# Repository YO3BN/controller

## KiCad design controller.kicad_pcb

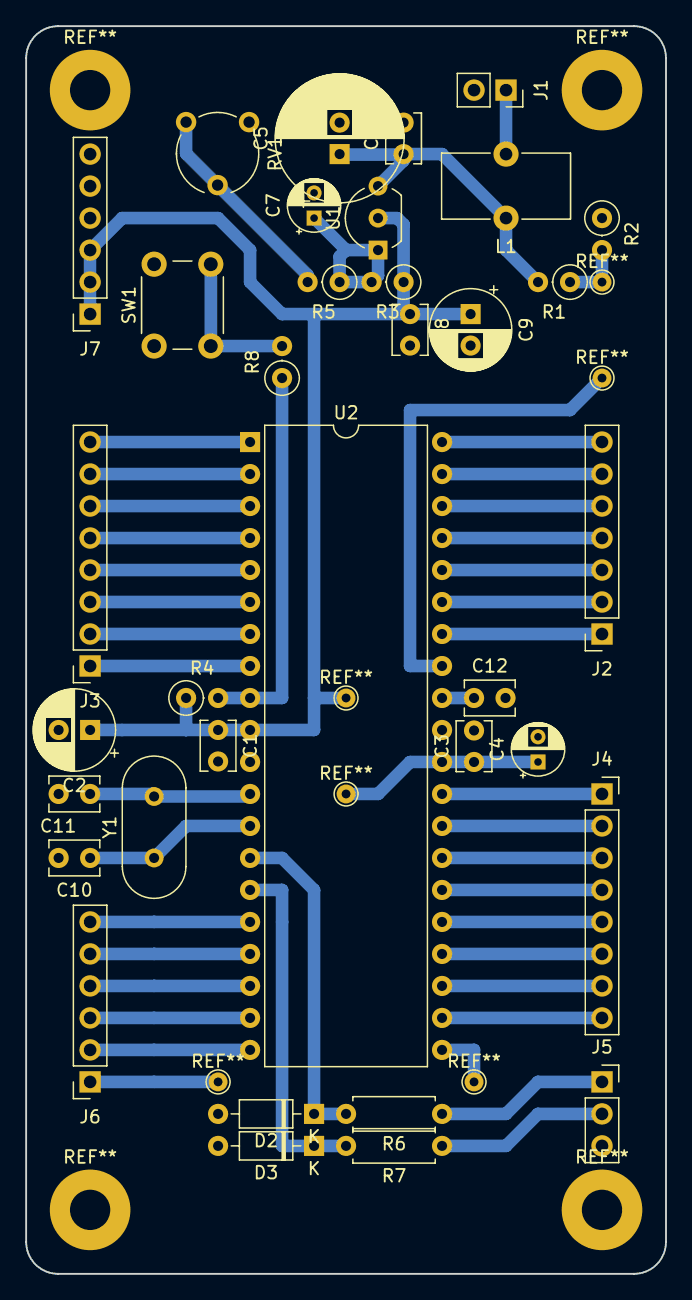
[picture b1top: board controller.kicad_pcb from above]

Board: 2 copper layers, 50.8 x 99.1 mm, 35 parts (0 on the bottom side), 45 nets.

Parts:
C1, C3, C6, C8, C12: 100n; C_Disc_D3.8mm_W2.6mm_P2.50mm
C2: 100u; CP_Radial_D6.3mm_P2.50mm
C4: 100u; CP_Radial_D4.0mm_P2.00mm
C5: 1000u; CP_Radial_D10.0mm_P2.50mm
C7: 1u; CP_Radial_D4.0mm_P2.00mm
C9: 220u; CP_Radial_D6.3mm_P2.50mm
C10, C11: 12p; C_Disc_D3.8mm_W2.6mm_P2.50mm
D2, D3: 5v6; D_DO-35_SOD27_P7.62mm_Horizontal
J1: +12V; PinSocket_1x02_P2.54mm_Vertical
J2: PA; PinSocket_1x07_P2.54mm_Vertical
J3: PB; PinSocket_1x08_P2.54mm_Vertical
J4: PC; PinSocket_1x08_P2.54mm_Vertical
J5: UART; PinSocket_1x03_P2.54mm_Vertical
J6: PD; PinSocket_1x06_P2.54mm_Vertical
J7: VDD OUT; PinSocket_1x06_P2.54mm_Vertical
L1: >=10mH; L_Toroid_Vertical_L10.0mm_W5.0mm_P5.08mm
R1: 68k; R_Axial_DIN0207_L6.3mm_D2.5mm_P2.54mm_Vertical
R2, R4: 10k; R_Axial_DIN0207_L6.3mm_D2.5mm_P2.54mm_Vertical
R3: 12k; R_Axial_DIN0207_L6.3mm_D2.5mm_P2.54mm_Vertical
R5: 15k; R_Axial_DIN0207_L6.3mm_D2.5mm_P2.54mm_Vertical
R6, R7: 560; R_Axial_DIN0207_L6.3mm_D2.5mm_P7.62mm_Horizontal
R8: 100; R_Axial_DIN0207_L6.3mm_D2.5mm_P2.54mm_Vertical
RV1: 10k; Potentiometer_Piher_PT-6-V_Vertical
SW1: RESET; SW_PUSH_6mm
U1: LM317L_TO92; TO-92_Inline_Wide
U2: ATmega1284-PU; DIP-40_W15.24mm
Y1: 20MHz; Crystal_HC49-U_Vertical

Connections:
GND: C1.2, C2.2, C3.2, C4.2, C5.2, C6.2, C7.2, C8.2, C9.2, C10.2, C11.2, C12.2, D2.2, D3.2, J1.2, J5.3, J7.4, J7.5, J7.6, R2.1, RV1.3, SW1.1, U2.11, U2.31
unnamed: C1.1, C2.1, C3.1, C4.1, C8.1, C9.1, J7.1, J7.2, J7.3, R3.1, R4.1, U1.2, U2.10, U2.30
unnamed: C5.1, C6.1, L1.1, R1.2, U1.3
unnamed: C7.1, R3.2, R5.1, U1.1
unnamed: C10.1, U2.13, Y1.1
unnamed: C11.1, U2.12, Y1.2
unnamed: C12.1, U2.32
unnamed: D2.1, R6.2, U2.14
unnamed: D3.1, R7.2, U2.15
unnamed: J1.1, L1.2
unnamed: J2.1, U2.34
unnamed: J2.2, U2.35
unnamed: J2.3, U2.36
unnamed: J2.4, U2.37
unnamed: J2.5, U2.38
unnamed: J2.6, U2.39
unnamed: J2.7, U2.40
unnamed: J3.1, U2.8
unnamed: J3.2, U2.7
unnamed: J3.3, U2.6
unnamed: J3.4, U2.5
unnamed: J3.5, U2.4
unnamed: J3.6, U2.3
unnamed: J3.7, U2.2
unnamed: J3.8, U2.1
unnamed: J4.1, U2.29
unnamed: J4.2, U2.28
unnamed: J4.3, U2.27
unnamed: J4.4, U2.26
unnamed: J4.5, U2.25
unnamed: J4.6, U2.24
unnamed: J4.7, U2.23
unnamed: J4.8, U2.22
unnamed: J5.1, R7.1
unnamed: J5.2, R6.1
unnamed: J6.1, U2.21
unnamed: J6.2, U2.20
unnamed: J6.3, U2.19
unnamed: J6.4, U2.18
unnamed: J6.5, U2.17
unnamed: J6.6, U2.16
unnamed: R1.1, R2.2, U2.33
unnamed: R4.2, R8.1, U2.9
unnamed: R5.2, RV1.1, RV1.2
unnamed: R8.2, SW1.2

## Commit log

2020-02-04 Initial Commit - Schematic - Footprints - Netlist - PCB layout
2022-07-19 -Improved noise filtering on supply rail (added L1 and increased C5 from 100 to 1000uF).
